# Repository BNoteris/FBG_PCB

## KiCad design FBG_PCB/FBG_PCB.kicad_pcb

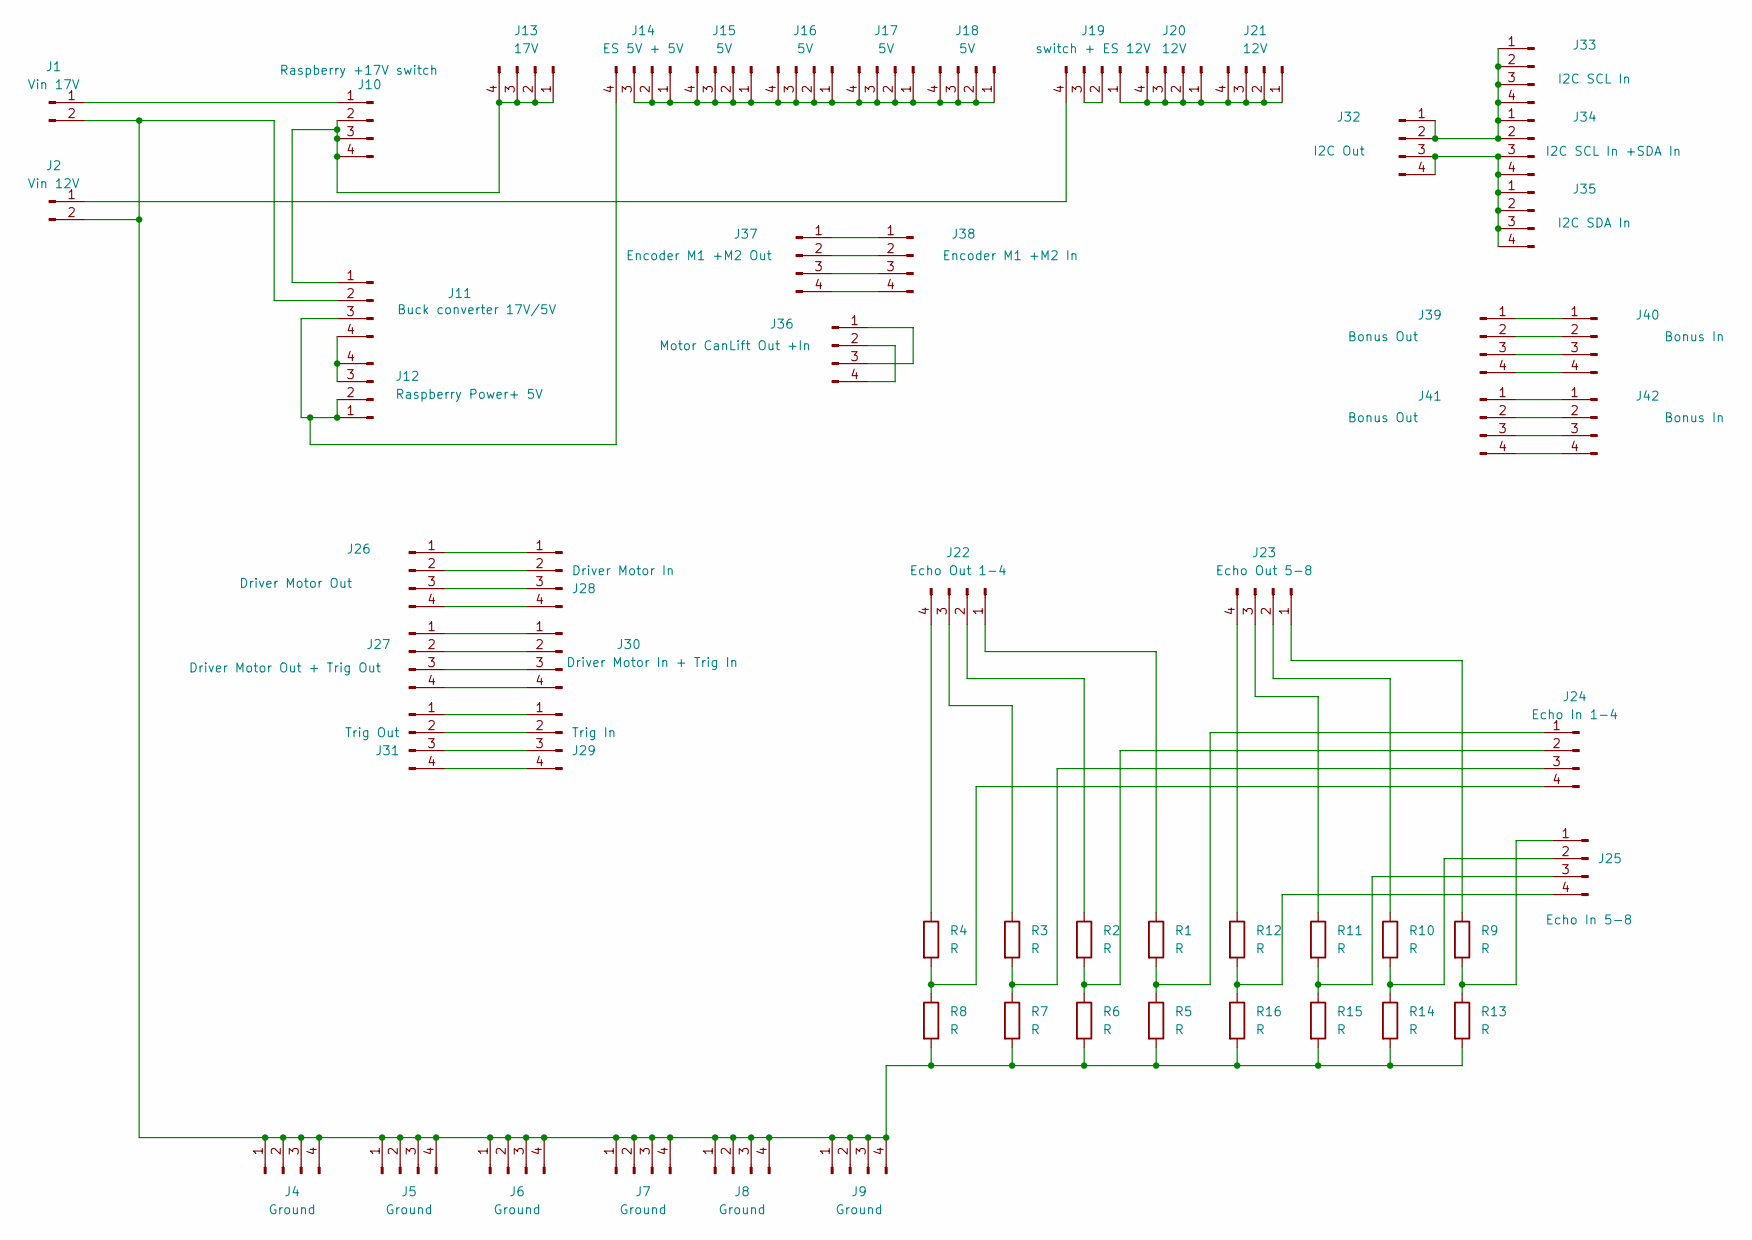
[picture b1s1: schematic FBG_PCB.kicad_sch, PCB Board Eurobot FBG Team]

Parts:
J1: Vin 17V; JST_NV_B02P-NV_1x02_P5.00mm_Vertical
J2: Vin 12V; JST_NV_B02P-NV_1x02_P5.00mm_Vertical
J4, J5, J6, J7, J8, J9: Ground; Molex_SL_171971-0004_1x04_P2.54mm_Vertical
J10: Raspberry +17V switch; Molex_SL_171971-0004_1x04_P2.54mm_Vertical
J11: Buck converter 17V/5V; Molex_SL_171971-0004_1x04_P2.54mm_Vertical
J12: Raspberry Power+ 5V; Molex_SL_171971-0004_1x04_P2.54mm_Vertical
J13: 17V; Molex_SL_171971-0004_1x04_P2.54mm_Vertical
J14: ES 5V + 5V; Molex_SL_171971-0004_1x04_P2.54mm_Vertical
J15, J16, J17, J18: 5V; Molex_SL_171971-0004_1x04_P2.54mm_Vertical
J19: switch + ES 12V; Molex_SL_171971-0004_1x04_P2.54mm_Vertical
J20, J21: 12V; Molex_SL_171971-0004_1x04_P2.54mm_Vertical
J22: Echo Out 1-4; Molex_SL_171971-0004_1x04_P2.54mm_Vertical
J23: Echo Out 5-8; Molex_SL_171971-0004_1x04_P2.54mm_Vertical
J24: Echo In 1-4; Molex_SL_171971-0004_1x04_P2.54mm_Vertical
J25: Echo In 5-8; Molex_SL_171971-0004_1x04_P2.54mm_Vertical
J26: Driver Motor Out; Molex_SL_171971-0004_1x04_P2.54mm_Vertical
J27: Driver Motor Out + Trig Out; Molex_SL_171971-0004_1x04_P2.54mm_Vertical
J28: Driver Motor In; Molex_SL_171971-0004_1x04_P2.54mm_Vertical
J29: Trig In; Molex_SL_171971-0004_1x04_P2.54mm_Vertical
J30: Driver Motor In + Trig In; Molex_SL_171971-0004_1x04_P2.54mm_Vertical
J31: Trig Out; Molex_SL_171971-0004_1x04_P2.54mm_Vertical
J32: I2C Out; Molex_SL_171971-0004_1x04_P2.54mm_Vertical
J33: I2C SCL In; Molex_SL_171971-0004_1x04_P2.54mm_Vertical
J34: I2C SCL In +SDA In; Molex_SL_171971-0004_1x04_P2.54mm_Vertical
J35: I2C SDA In; Molex_SL_171971-0004_1x04_P2.54mm_Vertical
J36: Motor CanLift Out +In; Molex_SL_171971-0004_1x04_P2.54mm_Vertical
J37: Encoder M1 +M2 Out; Molex_SL_171971-0004_1x04_P2.54mm_Vertical
J38: Encoder M1 +M2 In; Molex_SL_171971-0004_1x04_P2.54mm_Vertical
J39, J41: Bonus Out; Molex_SL_171971-0004_1x04_P2.54mm_Vertical
J40, J42: Bonus In; Molex_SL_171971-0004_1x04_P2.54mm_Vertical
R1, R2, R3, R4, R5, R6, R7, R8, R9, R10, R11, R12, R13, R14, R15, R16: R; R_Axial_DIN0207_L6.3mm_D2.5mm_P10.16mm_Horizontal

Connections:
unnamed: J1.1, J10.1
unnamed: J1.2, J2.2, J4.1, J4.2, J4.3, J4.4, J5.1, J5.2, J5.3, J5.4, J6.1, J6.2, J6.3, J6.4, J7.1, J7.2, J7.3, J7.4, J8.1, J8.2, J8.3, J8.4, J9.1, J9.2, J9.3, J9.4, J11.2, R5.2, R6.2, R7.2, R8.2, R13.2, R14.2, R15.2, R16.2
unnamed: J10.2, J10.3, J10.4, J11.1, J13.1, J13.2, J13.3, J13.4
unnamed: J11.3, J12.1, J12.2, J14.4
unnamed: J11.4, J12.3, J12.4
unnamed: J14.1, J14.2, J14.3, J15.1, J15.2, J15.3, J15.4, J16.1, J16.2, J16.3, J16.4, J17.1, J17.2, J17.3, J17.4, J18.1, J18.2, J18.3, J18.4
unnamed: J19.1, J20.1, J20.2, J20.3, J20.4, J21.1, J21.2, J21.3, J21.4
unnamed: J19.2, J19.3
unnamed: J2.1, J19.4
unnamed: J22.1, R1.1
unnamed: J22.2, R2.1
unnamed: J22.3, R3.1
unnamed: J22.4, R4.1
unnamed: J23.1, R9.1
unnamed: J23.2, R10.1
unnamed: J23.3, R11.1
unnamed: J23.4, R12.1
unnamed: J24.1, R1.2, R5.1
unnamed: J24.2, R2.2, R6.1
unnamed: J24.3, R3.2, R7.1
unnamed: J24.4, R4.2, R8.1
unnamed: J25.1, R9.2, R13.1
unnamed: J25.2, R10.2, R14.1
unnamed: J25.3, R11.2, R15.1
unnamed: J25.4, R12.2, R16.1
unnamed: J26.1, J28.1
unnamed: J26.2, J28.2
unnamed: J26.3, J28.3
unnamed: J26.4, J28.4
unnamed: J27.1, J30.1
unnamed: J27.2, J30.2
unnamed: J27.3, J30.3
unnamed: J27.4, J30.4
unnamed: J29.1, J31.1
unnamed: J29.2, J31.2
unnamed: J29.3, J31.3
unnamed: J29.4, J31.4
unnamed: J32.1, J32.2, J33.1, J33.2, J33.3, J33.4, J34.1, J34.2
unnamed: J32.3, J32.4, J34.3, J34.4, J35.1, J35.2, J35.3, J35.4
unnamed: J36.1, J36.3
unnamed: J36.2, J36.4
unnamed: J37.1, J38.1
unnamed: J37.2, J38.2
unnamed: J37.3, J38.3
unnamed: J37.4, J38.4
unnamed: J39.1, J40.1
unnamed: J39.2, J40.2
unnamed: J39.3, J40.3
unnamed: J39.4, J40.4
unnamed: J41.1, J42.1
unnamed: J41.2, J42.2
unnamed: J41.3, J42.3
unnamed: J41.4, J42.4

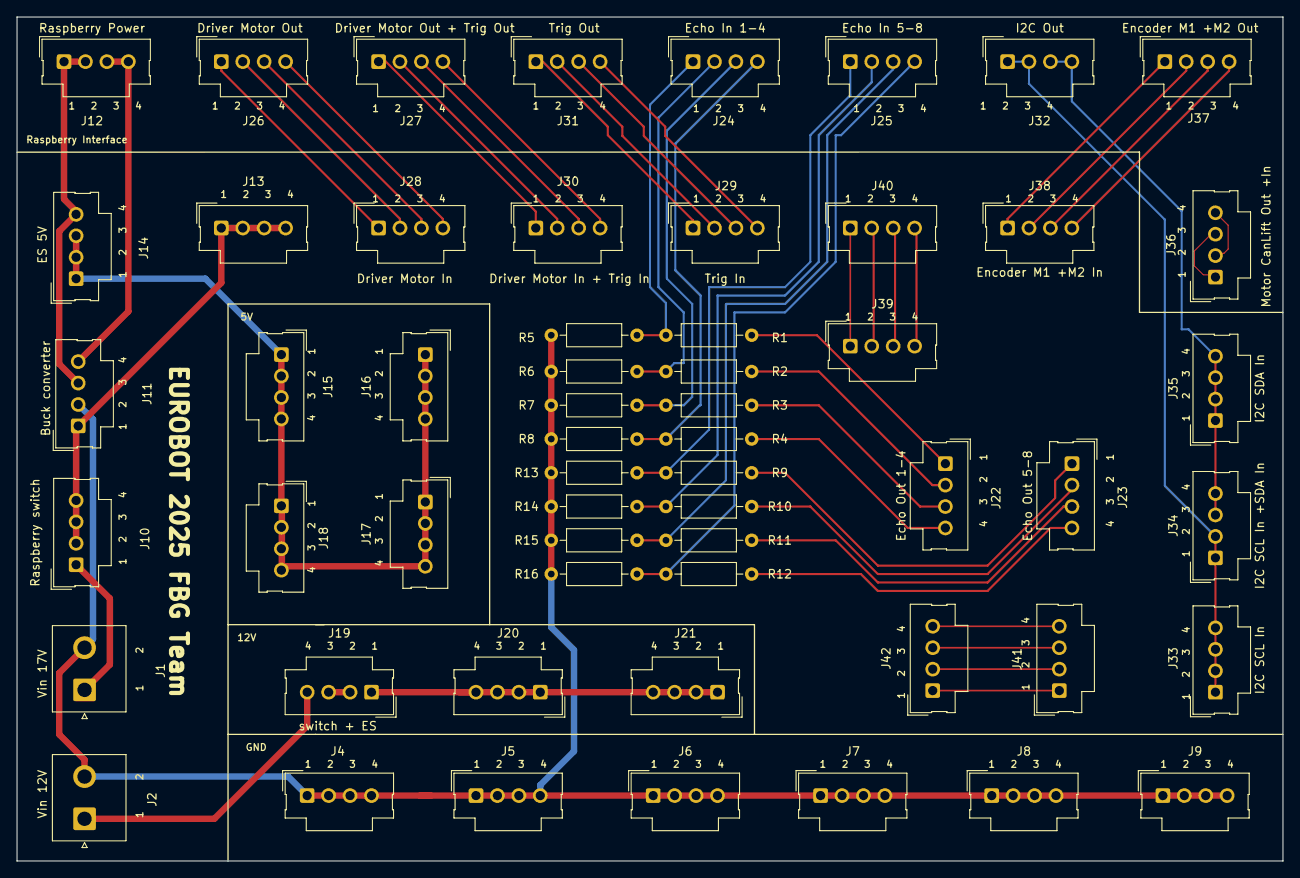
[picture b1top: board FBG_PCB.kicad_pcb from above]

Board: 4 copper layers, 150.0 x 100.0 mm, 57 parts (0 on the bottom side), 53 nets.

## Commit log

2025-03-12 Creation
2025-03-12 visu pcb update
2025-03-13 Lot of new connectors
2025-03-13 trig + echo
2025-03-15 V1.0
2025-03-15 V2.1
2025-03-17 gitignore
2025-03-17 schematics
